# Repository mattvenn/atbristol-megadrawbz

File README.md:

# @bristol energy drawing robot

## updates

* [youtube playlist](https://www.youtube.com/playlist?list=PLmcDgdDpcaPiOdnMplbk7o1K5Kpvp_UAL)
* [photos](https://goo.gl/photos/KGhmjEyrZScbemvW7)

## details

### hardware

* [Beagle bone breakout board](hardware/bbbbbb_pcb/)
* [Pen holder](hardware/gondola_pcb/)
* [notes on stepper choice](tests/stepper-choice)

### machinekit/linuxcnc configuration

* Robot is controlled with machinekit running on a beaglebone black.
* Pen holder is controlled via Xbee radio and uses a [custom component] that runs in its own realtime thread.

* [configuration](https://github.com/mattvenn/machinekit-bipod)

### firmware

* [pen holder firmware](firmware/gondola/)

### tests

* [prototypes, tests, proof of concepts](tests)

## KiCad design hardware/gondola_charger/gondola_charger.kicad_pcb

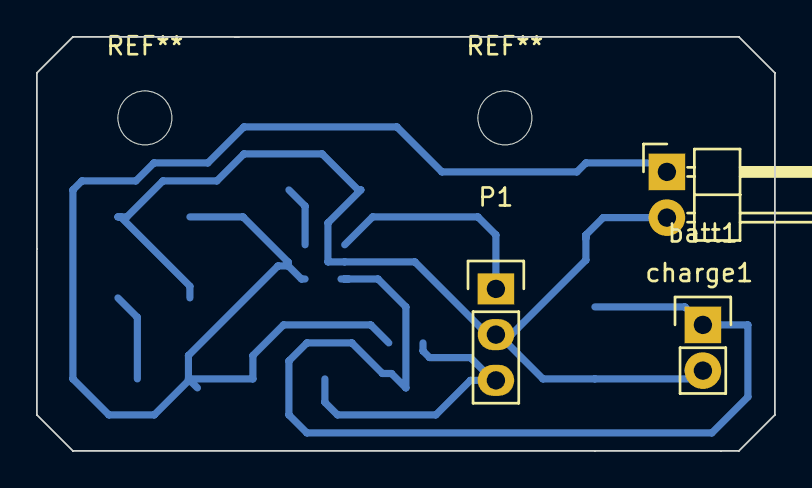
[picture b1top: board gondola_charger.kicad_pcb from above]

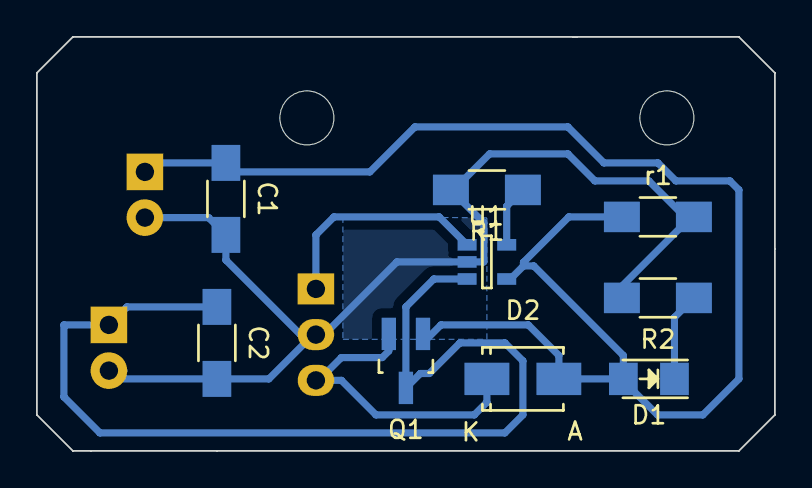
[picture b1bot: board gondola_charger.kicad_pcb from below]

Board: 2 copper layers, 41.0 x 23.0 mm, 12 parts (9 on the bottom side), 7 nets.

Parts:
C1, C2: 4.7u; C_1206_HandSoldering
D1: LED; LED-1206
D2: D_Schottky; SMA_Standard
P1: board conn; Pin_Header_Straight_1x03
Q1: Q_PMOS_GSD; SOT-23_Handsoldering
R1: 2k; R_1206_HandSoldering
R2: 500r; R_1206_HandSoldering
U1: MCP73832; SOT-23-5
batt1: CONN_01X02; Pin_Header_Straight_1x02
charge1: CONN_01X02; Pin_Header_Angled_1x02
r1: 100k; R_1206_HandSoldering

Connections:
+5V: C1.1, D1.2, D2.2, Q1.1, U1.4, charge1.1, r1.1
GND: C1.2, C2.2, P1.2, R1.2, R2.2, U1.2, batt1.2, charge1.2, r1.2
unnamed: D1.1, R2.1
unnamed: R1.1, U1.5
batt: C2.1, Q1.3, U1.3, batt1.1
charge_safe: P1.1, U1.1
powerout: D2.1, P1.3, Q1.2

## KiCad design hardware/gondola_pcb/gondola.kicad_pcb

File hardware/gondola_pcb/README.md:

# gondola PCB

## mods made

* connect xbee rx & tx to atmel rx & tx (no software serial) - solder wires to xbee header and connected a header that plugs into the programming header
* [lipo charger](http://dlnmh9ip6v2uc.cloudfront.net/datasheets/Prototyping/TP4056.pdf) soldered to the back, connected pin 7 to charge pin on pcb

## fixes required for next version

* lipo charger on board
* reset button
* reset xbee from atmega
* remote firmware update - arduino needs to reset itself 
* lipo socket that fits
* crystal footprint, no load caps required!
* lower frequency crtstal, mega328 is only guaranteed to 10mhz on 3.3v

## xbee firmware update

* has to be hw. tried sw and didn't work. used a 2n3904 to invert the signal and pull reset low
* haven't tried with xbee yet.
* wide timing window : 900ms before or after avrdude is run

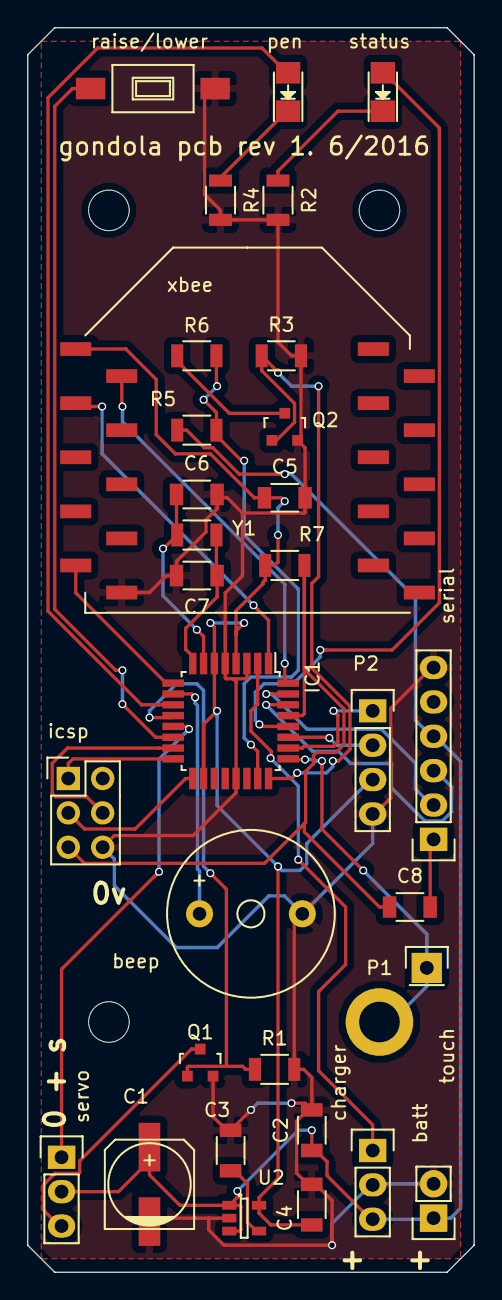
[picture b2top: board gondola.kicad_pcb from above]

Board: 2 copper layers, 33.0 x 92.0 mm, 33 parts (0 on the bottom side), 32 nets.

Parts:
C1: 100u; c_elec_6.3x5.3
C2: 1u; C_1206
C3: 0.01u; C_1206
C4, C5: 2.2u; C_1206
C6, C7: 20p; C_1206
C8: 100n; C_1206
IC1: ATMEGA328P-A; TQFP-32_7x7mm_Pitch0.8mm
P1: CONN_01X01; MountingHole_3mm
P2: CONN_01X04; Pin_Header_Straight_1x04
Q1, Q2: Q_NMOS_GSD; SOT-23
R1, R3: 10k; R_1206
R2, R4, R5, R6: R; R_1206
R7: 20k; R_1206
U2: LP2985LV; SOT-23-5
Y1: Crystal; R_1206
batt: CONN_01X02; Pin_Header_Straight_1x02
beep: CONN_01X02; Buzzer_12x9.5RM7.6
charger: CONN_01X03; Pin_Header_Straight_1x03
icsp: CONN_02X03; Pin_Header_Straight_2x03
pen: LED; LED-1206
raise/lower: SW_PUSH; SW_SPST_FSMSM
serial: CONN_01X06; Pin_Header_Straight_1x06
servo: CONN_01X03; Pin_Header_Straight_1x03
status: LED; LED-1206
touch: CONN_01X01; Pin_Header_Straight_1x01
xbee: xbee

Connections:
+3V3: C4.1, C5.1, IC1.4, IC1.6, IC1.18, P2.3, R7.1, U2.5, xbee.1
Earth: C1.2, C2.2, C3.2, C4.2, C5.2, C6.2, C7.2, IC1.3, IC1.5, IC1.21, P2.4, Q1.2, Q2.2, R1.2, R2.2, R3.2, R4.2, U2.2, batt.2, beep.2, charger.2, icsp.6, raise/lower.2, serial.6, xbee.10
unnamed: C3.1, U2.4
unnamed: C6.1, IC1.7, Y1.1
unnamed: C7.1, IC1.8, Y1.2
unnamed: R2.1, status.1
unnamed: R4.1, pen.1
unnamed: Q1.3, servo.3
unnamed: Q2.3, R6.2
batt-sense: IC1.23, R5.2, R6.1
batt_in: C1.1, C2.1, R5.1, U2.1, U2.3, batt.1, charger.3, serial.4, servo.2
beep: IC1.10, beep.1
button: IC1.14, raise/lower.1
charge: IC1.2, charger.1
divider: IC1.24, Q2.1, R3.1
dtr: C8.2, serial.1
gpio1: IC1.26, P2.1
gpio2: IC1.27, P2.2
miso: IC1.16, icsp.1
mosi: IC1.15, icsp.4
pen: IC1.11, pen.2
radio-sleep: IC1.9, xbee.9
reset: C8.1, IC1.29, R7.2, icsp.5
rx: IC1.30, serial.3
sck: IC1.17, icsp.3
servo: IC1.13, servo.1
servo-enable: IC1.12, Q1.1, R1.1
status: IC1.28, status.2
touch: IC1.25, P1.1, touch.1
tx: IC1.31, serial.2
xbee-rx: IC1.1, xbee.3
xbee-tx: IC1.32, xbee.2

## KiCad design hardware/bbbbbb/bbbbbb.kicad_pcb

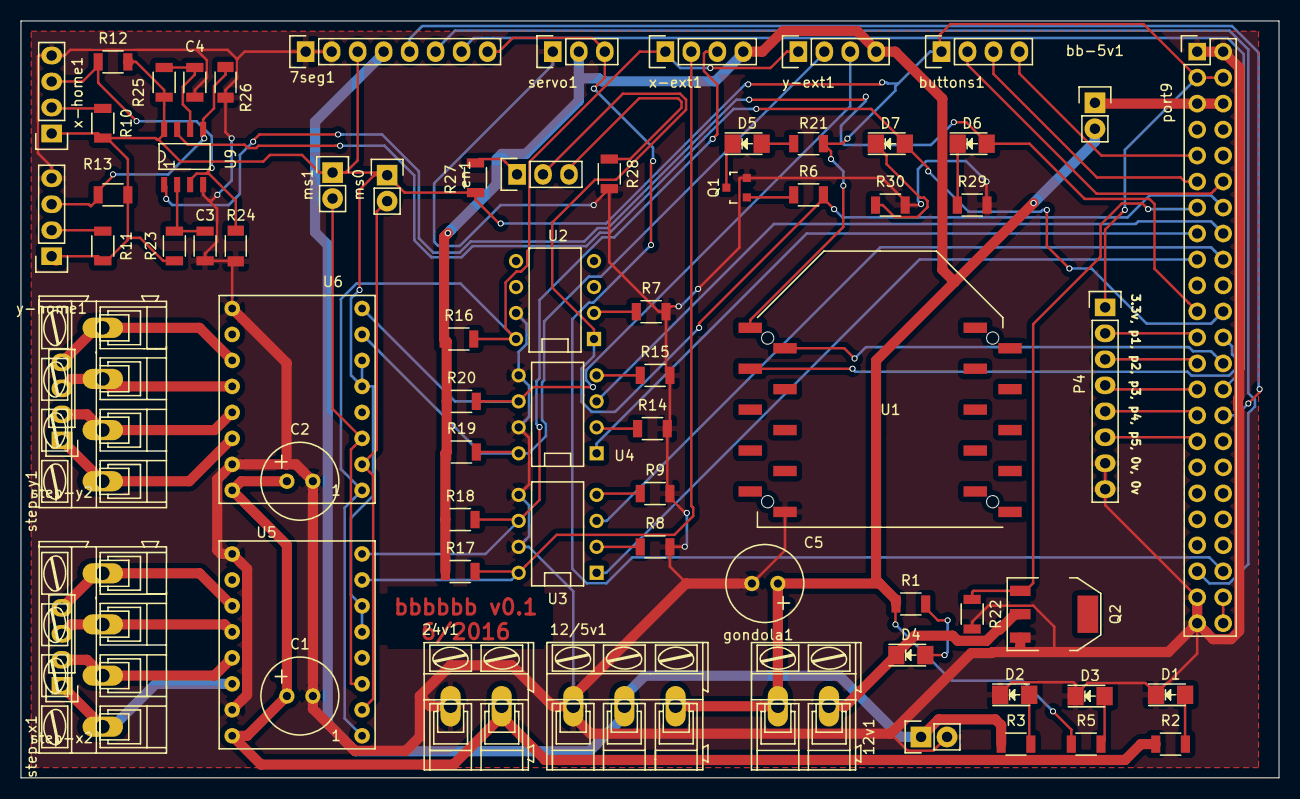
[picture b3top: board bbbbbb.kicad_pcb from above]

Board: 2 copper layers, 123.0 x 74.0 mm, 71 parts (0 on the bottom side), 67 nets.

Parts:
7seg1: 7seg; Pin_Header_Straight_1x08
12/5v1: 12/5v; AK300-3
12v1: fan; Pin_Header_Straight_1x02
24v1: 24v; AK300-2
C1, C2: 47uf; Elko_vert_11.2x7.5mm_RM2.5
C3, C4: 2.2n; C_1206
C5: 47u; Elko_vert_11.2x7.5mm_RM2.5
D1, D2, D3, D4, D5: LED; LED-1206
D6: x home; LED-1206
D7: y home; LED-1206
P4: CONN_01X08; Pin_Header_Straight_1x08
Q1: BC849C; SOT-23
Q2: pmt29en; SOT-223
R1, R5: 560; R_1206
R2: 4.7k; R_1206
R3, R24, R26: 2k; R_1206
R6, R7, R8, R9, R12, R13, R14, R15, R16, R17, R18, R19, R20: 1k; R_1206
R10, R11: 330; R_1206
R21, R29, R30: 220; R_1206
R22, R27, R28: 10k; R_1206
R23, R25: 8k; R_1206
U1: xbee
U2, U3, U4: LTV-827; DIP-8__300
U5, U6: drv2250; drv8825
U9: LM358; soic8
bb-5v1: bb-5v; Pin_Header_Straight_1x02
buttons1: buttons; Pin_Header_Straight_1x04
en1: enable pull up; Pin_Header_Straight_1x03
gondola1: gondola charge; AK300-2
ms0: ms0; Pin_Header_Straight_1x02
ms1: ms1; Pin_Header_Straight_1x02
port9: CONN_02X23; Pin_Header_Straight_2x23
servo1: servo; Pin_Header_Straight_1x03
step-x1: CONN_01X04; AK300-4
step-x2: CONN_01X04; Pin_Header_Straight_1x04
step-y1: CONN_01X04; AK300-4
step-y2: CONN_01X04; Pin_Header_Straight_1x04
x-ext1: CONN_01X04; Pin_Header_Straight_1x04
x-home1: CONN_01X04; Pin_Header_Straight_1x04
y-ext1: CONN_01X04; Pin_Header_Straight_1x04
y-home1: CONN_01X04; Pin_Header_Straight_1x04

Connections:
+3V3: 7seg1.3, P4.1, R10.2, R11.2, R12.2, R13.2, R21.1, R23.1, R25.1, R27.2, U1.1, U5.5, U5.6, U6.5, U6.6, U9.8, buttons1.1, ms0.1, ms1.1, port9.3, port9.4, x-home1.1, y-home1.1
+5V: 12/5v1.3, C5.1, R1.1, R5.1, R16.1, R17.1, R18.1, R19.1, R20.1, bb-5v1.2, gondola1.1, servo1.2, x-ext1.4, y-ext1.4
+12V: 7seg1.4, 12/5v1.2, 12v1.1, R3.1
+24V: 24v1.2, C1.1, C2.1, R2.1, U5.16, U6.16
/7seg-!oe: 7seg1.8, port9.42, servo1.3
/7seg-clk: 7seg1.6, port9.41
/7seg-le: 7seg1.7, port9.28
/7seg-sdo: 7seg1.5, port9.30
/bb-5v: bb-5v1.1, port9.5, port9.6
/butt-estop: buttons1.3, port9.11
/butt-power: buttons1.4, port9.9
/butt-reset: buttons1.2, port9.12
/enable-ext: R16.2, U2.8, U5.1, U6.1, x-ext1.1, y-ext1.1
/gpio1: P4.2, port9.23
/gpio2: P4.3, port9.25
/gpio3: P4.4, port9.27
/gpio4: P4.5, port9.29
/gpio5: P4.6, port9.31
/ms0: U5.2, U6.2, ms0.2
/ms1: U5.3, U6.3, ms1.2
/xbee-rx: U1.3, port9.24
/xbee-tx: U1.2, port9.26
/xdir: U3.3, port9.18
/xdir-ext: R18.2, U3.6, U5.8, x-ext1.3
/xstep: U3.1, port9.17
/xstep-ext: R17.2, U3.8, U5.7, x-ext1.2
/ydir: U4.3, port9.16
/ydir-ext: R20.2, U4.6, U6.8, y-ext1.3
/ystep: U4.1, port9.15
/ystep-ext: R19.2, U4.8, U6.7, y-ext1.2
Earth: 7seg1.1, 7seg1.2, 12/5v1.1, 12v1.2, 24v1.1, C1.2, C2.2, C3.1, C4.1, C5.2, D1.1, D2.1, D3.1, P4.7, P4.8, Q1.2, Q2.3, R7.2, R8.2, R9.2, R14.2, R15.2, R22.2, R24.2, R26.2, R28.2, R29.2, R30.2, U1.10, U2.7, U3.5, U3.7, U4.5, U4.7, U5.9, U5.15, U6.9, U6.15, U9.4, port9.1, port9.2, port9.43, port9.45, servo1.1, x-home1.4, y-home1.4
unnamed: C3.2, R12.1, U9.3, x-home1.3
unnamed: C4.2, R13.1, U9.5, y-home1.3
unnamed: D1.2, R2.2
unnamed: D2.2, R3.2
unnamed: D3.2, R5.2
unnamed: D4.1, Q2.2, gondola1.2
unnamed: D4.2, R1.2
unnamed: D5.1, Q1.3
unnamed: D5.2, R21.2
unnamed: D6.1, R29.1
unnamed: D7.1, R30.1
unnamed: Q1.1, R6.1
unnamed: R7.1, U2.2
unnamed: R8.1, U3.2
unnamed: R9.1, U3.4
unnamed: R10.1, x-home1.2
unnamed: R11.1, y-home1.2
unnamed: R14.1, U4.2
unnamed: R15.1, U4.4
unnamed: R23.2, R24.1, U9.2
unnamed: R25.2, R26.1, U9.6
unnamed: R27.1, en1.1
unnamed: R28.1, en1.3
unnamed: U5.11, step-x1.4, step-x2.4
unnamed: U5.12, step-x1.3, step-x2.3
unnamed: U5.13, step-x1.2, step-x2.2
unnamed: U5.14, step-x1.1, step-x2.1
unnamed: U6.11, step-y1.4, step-y2.4
unnamed: U6.12, step-y1.3, step-y2.3
unnamed: U6.13, step-y1.2, step-y2.2
unnamed: U6.14, step-y1.1, step-y2.1
unnamed: port9.44, port9.46
enable: R6.2, U2.1, en1.2, port9.14
gondola-charge: Q2.1, R22.1, port9.13
x-home: D6.2, U9.1, port9.21
y-home: D7.2, U9.7, port9.22

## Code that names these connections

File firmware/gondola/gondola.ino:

//#include <SoftwareSerial.h>
#include <Servo.h>

#define LED_PEN 7
#define LED_STATUS A5
#define BEEP 6
#define XBEE_SLEEP 5

#define SERVO_ENABLE 8
#define SERVO 9
#define BUTTON 10

#define BATT_SENSE A0
#define BATT_DIVIDER A1
#define TOUCH A2
#define CHARGE 4

#define SERVO_MAX 160 //startup servo position hitec hs-81
#define SERVO_MIN 20
#define MON_INTERVAL 1000 //delay between reading ADC

#define AVG_NUM 10000 //filter for the touch,

int raw = 0;
unsigned long total = 0;
int samples = 0;
int average = 0;
uint8_t last_amount = 0;
struct {
    uint8_t start;
    uint8_t amount;
    uint8_t flags;
    uint8_t cksum;
} rx;

struct {
    uint8_t start = 0xAA;
    uint16_t batt;
    uint16_t rx_count;
    uint16_t err_count;
    uint8_t touch;
    uint8_t flags;
    uint8_t cksum;
} tx;

char rx_buf[sizeof(rx)];
char tx_buf[sizeof(tx)];

enum flags {
  FLAG_CHARGE        = 0b00000001,
  FLAG_SERVO_ENABLE  = 0b00000010,
};


Servo servo;
byte CRC8(char *data, byte len);
uint16_t read_batt_mv();

unsigned long mon_count = 0;
unsigned long touch_count = 0;
int touch_val = 0;
bool servo_enable = false;

void setup()
{
  //turn on xbee
  pinMode(XBEE_SLEEP, OUTPUT);
  digitalWrite(XBEE_SLEEP, LOW);

  servo.attach(SERVO);
  pinMode(SERVO_ENABLE, OUTPUT);
  digitalWrite(SERVO_ENABLE, HIGH);
  delay(10);
  servo.write(SERVO_MAX); // move to pen up
  delay(200);
  digitalWrite(SERVO_ENABLE, LOW);

  pinMode(BATT_DIVIDER, OUTPUT);
  digitalWrite(BATT_DIVIDER, LOW);

  Serial.begin(57600);

  pinMode(LED_PEN,OUTPUT);
  pinMode(LED_STATUS,OUTPUT);

  digitalWrite(LED_PEN,HIGH);
  digitalWrite(LED_STATUS,HIGH);

  pinMode(CHARGE, INPUT);
  digitalWrite(CHARGE, HIGH);

  pinMode(BUTTON, INPUT);
  digitalWrite(BUTTON, HIGH);


  tone(BEEP, 5000, 200);
  delay(200);

  tone(BEEP, 3000, 200);
}

uint16_t read_batt_mv()
{
    /* 
    R1 = 10k, R2 = 4.7k
    mv per ADC count = 3300 / 1024
    */
    digitalWrite(BATT_DIVIDER, HIGH);
    delay(2);
    return 4.737 * analogRead(BATT_SENSE);
    digitalWrite(BATT_DIVIDER, LOW);
}
void loop()
{
    // periodically update battery and print stats
    if(millis() > mon_count + MON_INTERVAL)
    {
        mon_count = millis();
        tx.batt = read_batt_mv();

        //charging flag
        /*
        Shutdown Hi-Z 
        No Battery Present Hi-Z 
        Preconditioning L 
        Constant-Current Fast Charge L
        Constant Voltage L
        Charge Complete – Standby H
        */
        if(digitalRead(CHARGE) == LOW) // charging
        {
            digitalWrite(LED_PEN, LOW);
            tx.flags |= FLAG_CHARGE;
        }
        else
        {
            tx.flags &= ~ FLAG_CHARGE;
            digitalWrite(LED_PEN, HIGH);
        }

        if(servo_enable)
            tx.flags |= FLAG_SERVO_ENABLE;
        else
            tx.flags &= ~ FLAG_SERVO_ENABLE;
    }

    if(Serial.available() >= sizeof(rx))
    {
        uint8_t start = Serial.peek();

        if(start != 0xAA)
        {
            // chuck the 1st byte
            Serial.read();
            tx.err_count ++;
            return;
        }
        
        digitalWrite(LED_STATUS,HIGH);
        Serial.readBytes(rx_buf, sizeof(rx));
        tx.rx_count ++;

        //copy buffer to structure
        memcpy(&rx, &rx_buf, sizeof(rx));
        //calculate cksum is ok
        if(rx.cksum != CRC8(rx_buf,sizeof(rx)-1))
        {
            //ignore broken packet
            //Serial.println("err: ck");
            tx.err_count ++;
        }
        else
        {
            //turn on or off servo
            if(rx.flags & FLAG_SERVO_ENABLE)
            {
                servo_enable = true;
                digitalWrite(SERVO_ENABLE, HIGH);
            }
            else
            {
                servo_enable = false;
                digitalWrite(SERVO_ENABLE, LOW);
            }

            //update the servo
            if(rx.amount <= SERVO_MAX && rx.amount >= SERVO_MIN)
                servo.write(rx.amount);
        }
        //send data back
        memcpy(&tx_buf, &tx, sizeof(tx));
        tx.cksum = CRC8(tx_buf,sizeof(tx)-1);

        memcpy(&tx_buf, &tx, sizeof(tx));
        Serial.write(tx_buf, sizeof(tx));

        digitalWrite(LED_STATUS,LOW);
    }
}

//crc from Dallas Semi
byte CRC8(char *data, byte len) 
{
    byte crc = 0x00;
    while (len--)
    {
        byte extract = *data++;
        for (byte tempI = 8; tempI; tempI--) 
        {
            byte sum = (crc ^ extract) & 0x01;
            crc >>= 1;
            if(sum) 
            {
                crc ^= 0x8C;
            }
            extract >>= 1;
        }
    }
    return crc;
}

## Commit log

2016-04-10 just turn it on
2016-04-10 fix range
2016-04-10 more testing - abandoned now
2016-04-10 supervisor config file
2016-04-10 work around broken adafruit library
2016-05-13 screwthread testing
2016-05-13 test fixture is square
2016-05-13 triangle errors!
2016-05-14 setup
2016-05-14 better res
2016-05-14 step test removed
2016-05-14 titles
2016-05-14 updated graphs
2016-05-14 clearer explanation
2016-05-14 fix bug in program that makes bad step amounts
2016-05-14 put plot back to how I expect things to work
2016-05-14 makefile
2016-05-17 dir structure
2016-05-18 wrong place
2016-05-18 preliminary schematics
2016-05-19 servo test
2016-05-19 new reciever sch
2016-05-19 1st reciever pcb
2016-05-20 emitter 1st pcb
2016-05-20 better dir struct, and some tweaks to pcbs
2016-05-23 not working
2016-05-23 first test
2016-05-23 readme
2016-05-23 more files
2016-05-23 home testing
2016-05-23 pics
2016-05-24 removed old files
2016-05-24 new graph
2016-05-24 submodule
2016-05-24 checkpoints revised with Matt, new footprints
2016-05-25 testing xbee
2016-05-25 last touches befor OSHP
2016-05-25 1mm dyneema test
2016-05-26 new tests
2016-05-26 fixed links
2016-05-31 full BOMs
2016-05-31 full BOMs again...
2016-06-01 notes
2016-06-10 slide homing
2016-06-13 test results for slider
2016-06-13 photo
2016-06-13 part number
2016-06-13 bit more intro
2016-06-13 fixed pic
2016-06-13 vid link
2016-06-13 mostly laid out
2016-06-13 first pass pcb layout
2016-06-14 footprints mostly done
2016-06-14 gondola charge
2016-06-16 stepper choices
2016-06-16 documented option
2016-06-16 silkscreen & values
2016-06-17 cap touch demo
2016-06-17 added video
2016-06-17 edit
2016-06-20 added lcd
2016-06-20 renamed
2016-06-20 gondola pcb
2016-06-22 gondola pcb to fab
2016-06-22 fixed solder mask over touch ring
2016-06-24 oshpark fab
2016-06-28 temp sense
2016-06-28 ignore
2016-06-28 cksum not working
2016-06-28 param
2016-06-29 working ok at 25ms, hal ok
2016-06-29 fixed cksum, better pin names
2016-06-30 deal with too many bytes
2016-06-30 removed old submodule
2016-06-30 moved can to gondola
2016-06-30 added new submodule
2016-06-30 typo
2016-06-30 link
2016-06-30 test canges
2016-06-30 data files
2016-06-30 rename
2016-06-30 stepper choice
2016-06-30 xbee lib
2016-06-30 libs
2016-06-30 moved to machinekit config repo
2016-06-30 test
2016-06-30 deleting xbee stuff
2016-06-30 count rx packets
2016-07-01 test xbee
2016-07-01 test probably duplicate of that in the machinekit repo
2016-07-02 gondola monitoring
2016-07-02 fix debug print
2016-07-05 added touch sense
2016-07-09 got pwm working by using /sys
2016-07-09 get rid of swserial as it causes servo jitter
2016-07-09 delay necessary to get adc flushed
2016-07-12 missing r values
2016-07-12 netlist
2016-07-12 fixed cap val
2016-07-12 test all pins
2016-07-13 tcn75 temp
2016-07-15 fixed stupid serial comms error, added charge flag
2016-07-18 pattern ideas
2016-07-23 constants
2016-07-24 sunny webbox
2016-07-27 freeboard dashboard
2016-07-28 show energy on the big digits
2016-08-01 mirror test
2016-08-01 tested local
2016-08-01 track error
2016-08-01 code for the big digits
2016-08-01 accidentally added all the files
2016-08-01 gitignore
2016-08-02 crontab
2016-08-29 submodule updates
2016-09-01 schematic
2016-09-08 battery usage pic
2016-09-09 turn off servo when charging
2016-09-09 code for enabling servo
2016-09-19 removed unused adctouch lib
2016-09-19 gondola pic
2016-10-04 notes on charger chip
2016-10-04 xbee config
2016-10-19 sleep on xbee pin, dont boot till voltage is >3500mv
2016-10-19 added @bristol config
2016-10-19 info about xbee programming
2016-10-20 found random power down issue
2016-10-24 gondola charger addon board
2016-10-24 just start up
2016-10-25 return a reply even in the event of a broken cksum
2016-10-26 start byte
2016-10-27 mcp73832 and extra hole
2016-10-27 final version
2016-11-02 low power test
2016-11-07 gondola fix notes
2016-11-07 image fix
2016-11-07 magnet idea
2016-11-17 firmware for November fix
2016-11-17 bipod for November fix
2017-06-30 root crontab
2017-07-02 new energy key
2017-07-02 fix log
2017-07-03 blanket exception handling
